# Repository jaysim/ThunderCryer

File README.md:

ThunderCryer
============

Alarm Clock 

new Variant started from scratch using ChibiosRT and uGFX

Modtivation is to get a more cleaner implementation and save time implenting a Graphics System. 

Plan is to use Chibios HAL as far as possible and use STM32USB_Host lib for MSC Host implementation

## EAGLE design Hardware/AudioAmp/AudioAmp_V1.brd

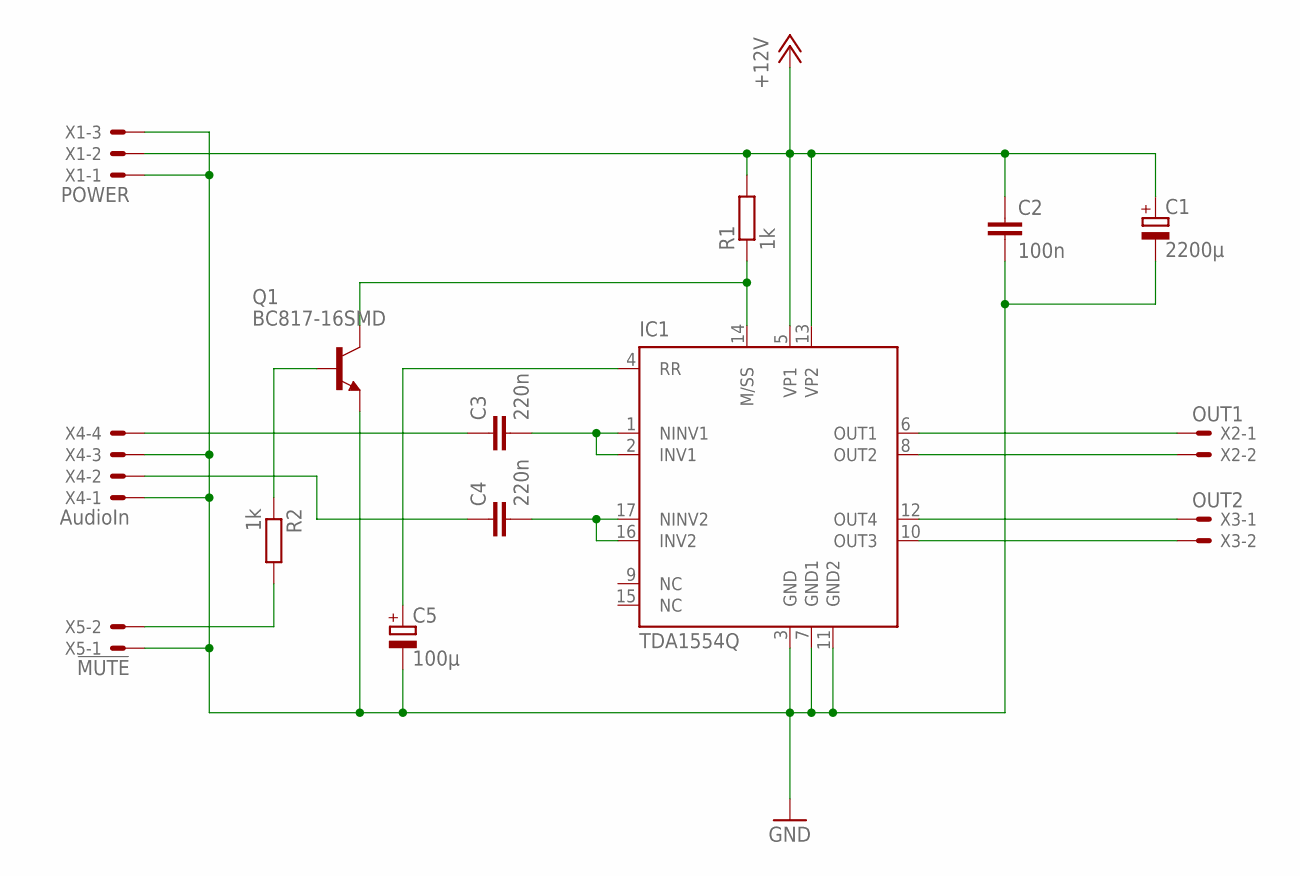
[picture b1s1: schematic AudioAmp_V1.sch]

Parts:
C1: 2200µ; E7,5-18
C2: 100n; C050-025X075
C3, C4: 220n; C050-025X075
C5: 100µ; E2,5-7
IC1: TDA1554Q; MULTIWAT-SIL17
Q1: BC817-16SMD; SOT23-BEC
R1, R2: 1k; 0204/7
X1: POWER; 22-23-2031
X2: OUT1; 22-23-2021
X3: OUT2; 22-23-2021
X4: AudioIn; 22-23-2041
X5: !MUTE; 22-23-2021

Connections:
+12V: C1.+, C2.1, IC1.5 (VP1), IC1.13 (VP2), R1.2, X1.2
GND: C1.-, C2.2, C5.-, IC1.3 (GND), IC1.7 (GND1), IC1.11 (GND2), Q1.E, X1.1, X1.3, X4.1, X4.3, X5.1
unnamed: C3.2, IC1.1 (NINV1), IC1.2 (INV1)
unnamed: C4.2, IC1.16 (INV2), IC1.17 (NINV2)
unnamed: R2.2, X5.2
unnamed: C4.1, X4.2
unnamed: C3.1, X4.4
unnamed: C5.+, IC1.4 (RR)
unnamed: Q1.B, R2.1
unnamed: IC1.10 (OUT3), X3.2
unnamed: IC1.12 (OUT4), X3.1
unnamed: IC1.8 (OUT2), X2.2
unnamed: IC1.6 (OUT1), X2.1
unnamed: IC1.14 (M/SS), Q1.C, R1.1

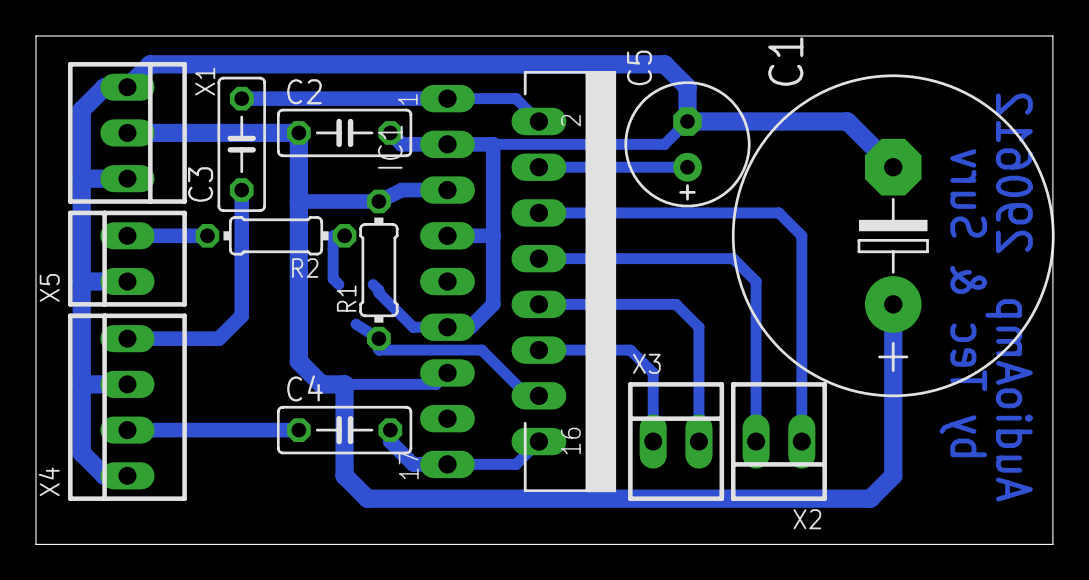
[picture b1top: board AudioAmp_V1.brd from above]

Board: 2 copper layers, 56.5 x 28.2 mm, 14 parts (1 on the bottom side), 14 nets.

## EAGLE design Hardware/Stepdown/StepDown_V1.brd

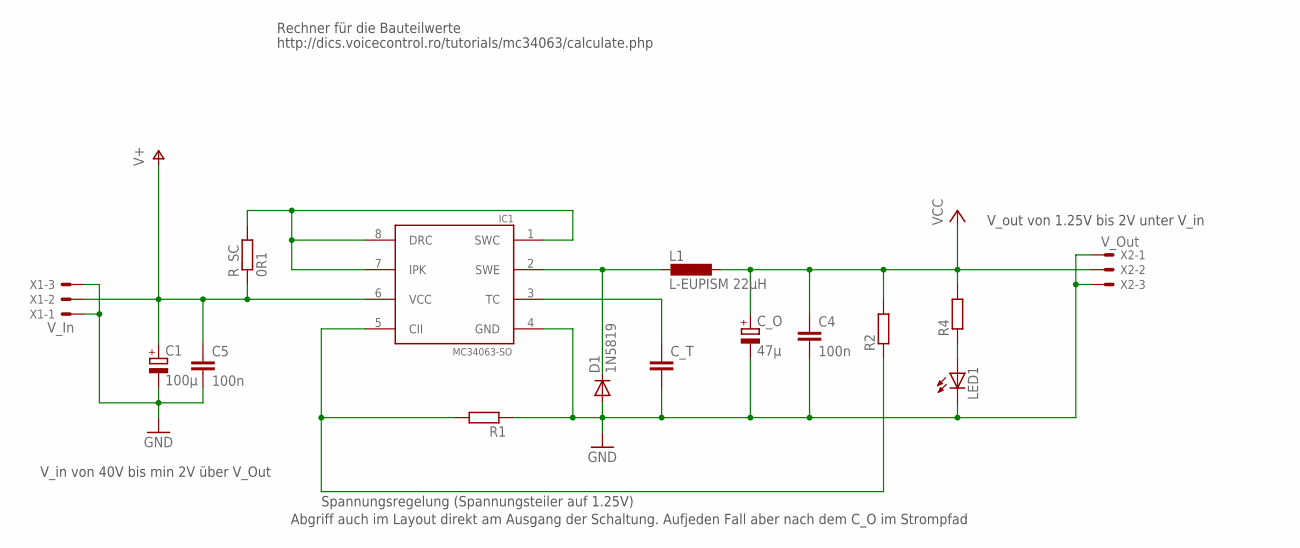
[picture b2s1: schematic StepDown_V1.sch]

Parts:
C1: 100µ; E2,5-7
C4, C5: 100n; C1206
C_O: 47µ; E2,5-7
C_T: C-EUC1206; C1206
D1: 1N5819; DO41-10
IC1: MC34063-SO; SO8
L1: L-EUPISM 22µH; PISM
LED1: LEDSML1206; SML1206
R1, R2, R4: R-EU_R1206; R1206
R_SC: 0R1; R1206
X1: V_In; 22-23-2031
X2: V_Out; 22-23-2031

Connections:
GND: C1.-, C4.2, C5.2, C_O.-, C_T.2, D1.A, IC1.4 (GND), LED1.C, R1.1, X1.1, X1.3, X2.1, X2.3
unnamed: IC1.1 (SWC), IC1.7 (IPK), IC1.8 (DRC), R_SC.2
unnamed: D1.C, IC1.2 (SWE), L1.2
unnamed: LED1.A, R4.1
unnamed: IC1.5 (CII), R1.2, R2.1
unnamed: C_T.1, IC1.3 (TC)
V+: C1.+, C5.1, IC1.6 (VCC), R_SC.1, X1.2
VCC: C4.1, C_O.+, L1.1, R2.2, R4.2, X2.2

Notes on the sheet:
http://dics.voicecontrol.ro/tutorials/mc34063/calculate.php
Rechner für die Bauteilwerte
V_in von 40V bis min 2V über V_Out
V_out von 1.25V bis 2V unter V_in
Spannungsregelung (Spannungsteiler auf 1.25V)
Abgriff auch im Layout direkt am Ausgang der Schaltung. Aufjeden Fall aber nach dem C_O im Strompfad

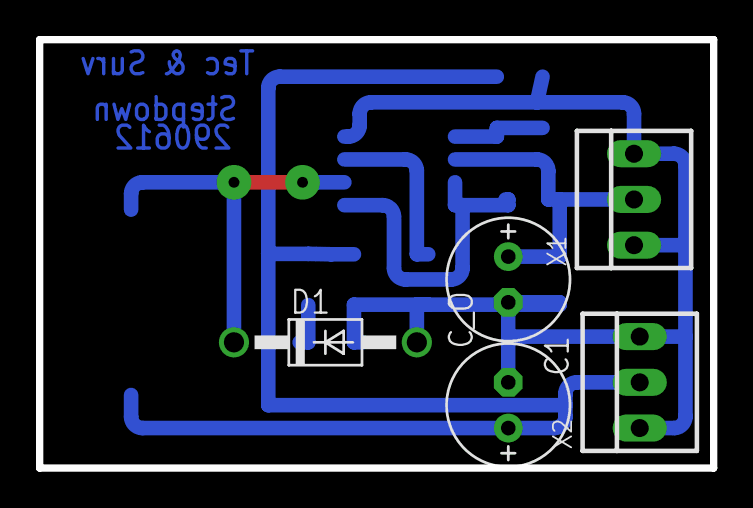
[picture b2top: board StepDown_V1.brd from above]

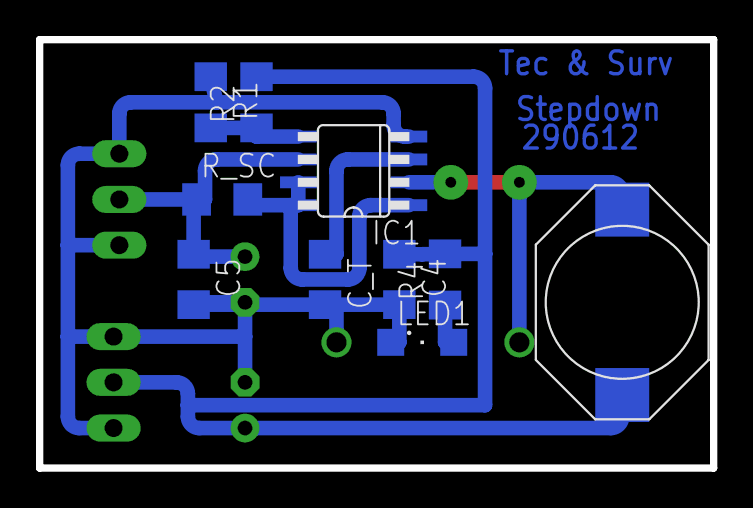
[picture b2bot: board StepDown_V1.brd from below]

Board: 2 copper layers, 37.4 x 23.8 mm, 15 parts (10 on the bottom side), 8 nets.

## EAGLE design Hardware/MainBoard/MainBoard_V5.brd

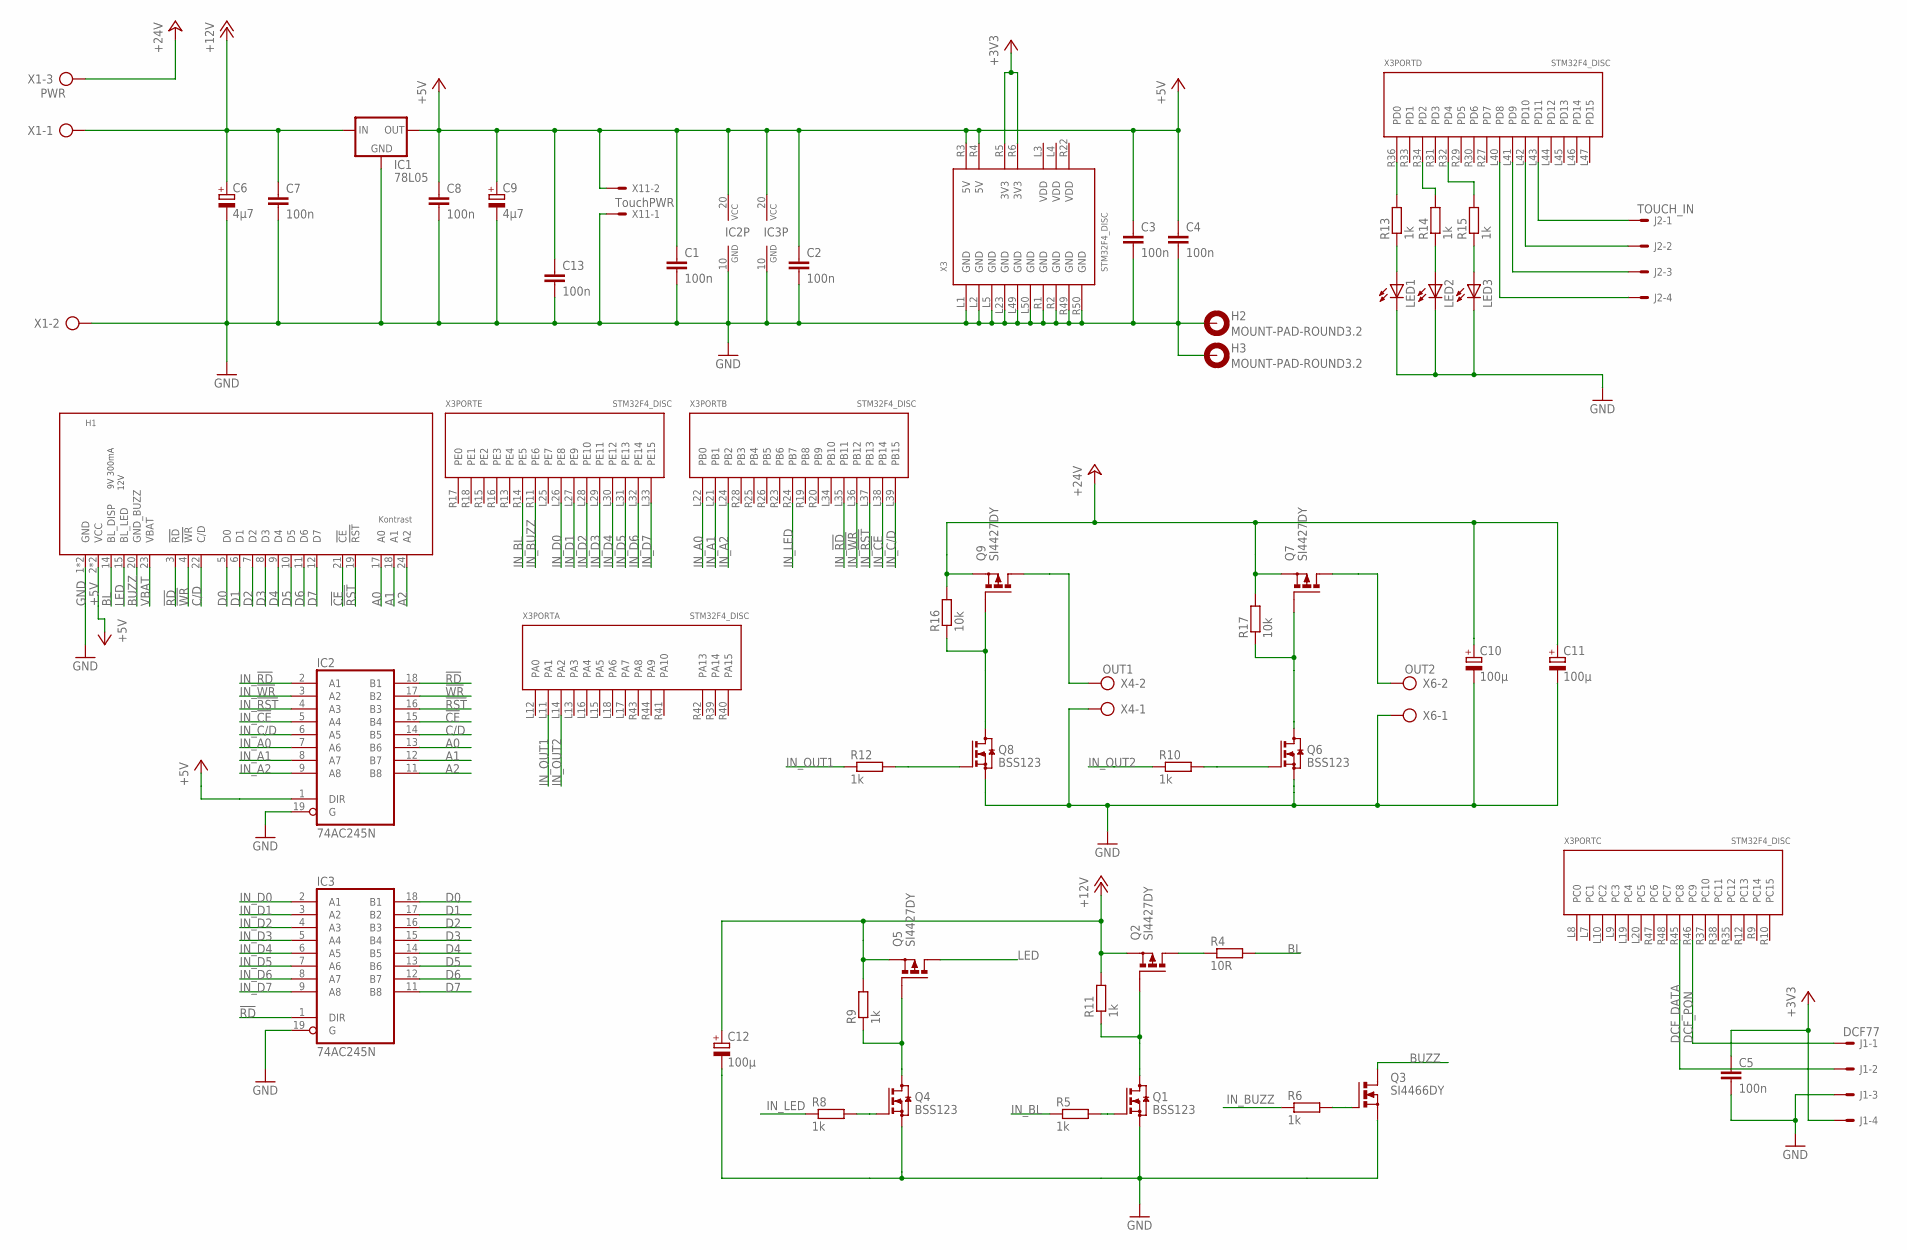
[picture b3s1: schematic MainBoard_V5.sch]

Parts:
C1, C2, C3, C4, C5, C7, C8, C13: 100n; C1206
C6, C9: 4µ7; E2-5
C10, C11, C12: 100µ; E2-5
H1: YL_24012-70-MICROMATCH; YL24012-70-MICROMATCH
H2, H3: MOUNT-PAD-ROUND3.2; 3,2-PAD
IC1: 78L05; 78XXS
IC2, IC3: 74AC245N; DIL20
J1: DCF77; 6410-04
J2: TOUCH_IN; 6410-04
LED1, LED2, LED3: LED3MM
Q1, Q4, Q6, Q8: BSS123; SOT23
Q2, Q5, Q7, Q9: SI4427DY; SO-08
Q3: SI4466DY; SO-08
R4: 10R; 0414/15
R5, R8, R9, R10, R11, R12, R13, R14, R15: 1k; 0207/10
R6: 1k; R0805
R16, R17: 10k; R1206
X1: PWR; AK500/3
X3: STM32F4_DISC
X4: OUT1; AK500/2
X6: OUT2; AK500/2
X11: TouchPWR; 22-23-2021

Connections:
!CE: H1.21 (!CE), IC2.15 (B4)
!RD: H1.3 (!RD), IC2.18 (B1), IC3.1 (DIR)
!RST: H1.19 (!RST), IC2.16 (B3)
!WR: H1.4 (!WR), IC2.17 (B2)
+3V3: C5.1, J1.4, X3.R5 (3V3), X3.R6 (3V3)
+5V: C1.1, C2.1, C3.1, C4.1, C8.1, C9.+, C13.1, H1.2 (VCC), H1.16 (VCC), IC1.OUT, IC2.1 (DIR), IC2.20 (VCC), IC3.20 (VCC), X3.R3 (5V), X3.R4 (5V), X11.2
+12V: C6.+, C7.1, C12.+, IC1.IN, Q2.1 (S), Q2.2 (S), Q2.3 (S), Q5.1 (S), Q5.2 (S), Q5.3 (S), R9.2, R11.2, X1.1
+24V: C10.+, C11.+, Q7.1 (S), Q7.2 (S), Q7.3 (S), Q9.1 (S), Q9.2 (S), Q9.3 (S), R16.2, R17.2, X1.3
A0: H1.17 (A0), IC2.13 (B6)
A1: H1.18 (A1), IC2.12 (B7)
A2: H1.24 (A2), IC2.11 (B8)
BL: H1.14 (BL_DISP), R4.2
BUZZ: H1.20 (GND_BUZZ), Q3.5 (D), Q3.6 (D), Q3.7 (D), Q3.8 (D)
C/D: H1.22 (C/D), IC2.14 (B5)
D0: H1.5 (D0), IC3.18 (B1)
D1: H1.6 (D1), IC3.17 (B2)
D2: H1.7 (D2), IC3.16 (B3)
D3: H1.8 (D3), IC3.15 (B4)
D4: H1.9 (D4), IC3.14 (B5)
D5: H1.10 (D5), IC3.13 (B6)
D6: H1.11 (D6), IC3.12 (B7)
D7: H1.12 (D7), IC3.11 (B8)
DCF_DATA: J1.2, X3.R45 (PC8)
DCF_PON: J1.1, X3.R46 (PC9)
GND: C1.2, C2.2, C3.2, C4.2, C5.2, C6.-, C7.2, C8.2, C9.-, C10.-, C11.-, C12.-, C13.2, H1.1 (GND), H1.13 (GND), H2.B3,2, H3.B3,2, IC1.GND, IC2.10 (GND), IC2.19 (G), IC3.10 (GND), IC3.19 (G), J1.3, LED1.K (C), LED2.K (C), LED3.K (C), Q1.2 (S), Q3.1 (S), Q3.2 (S), Q3.3 (S), Q4.2 (S), Q6.2 (S), Q8.2 (S), X1.2, X3.L1 (GND), X3.L2 (GND), X3.L5 (GND), X3.L23 (GND), X3.L49 (GND), X3.L50 (GND), X3.R1 (GND), X3.R2 (GND), X3.R49 (GND), X3.R50 (GND), X4.1, X6.1, X11.1
IN_!CE: IC2.5 (A4), X3.L38 (PB14)
IN_!RD: IC2.2 (A1), X3.L35 (PB11)
IN_!RST: IC2.4 (A3), X3.L37 (PB13)
IN_!WR: IC2.3 (A2), X3.L36 (PB12)
IN_A0: IC2.7 (A6), X3.L22 (PB0)
IN_A1: IC2.8 (A7), X3.L21 (PB1)
IN_A2: IC2.9 (A8), X3.L24 (PB2)
IN_BL: R5.1, X3.R14 (PE5)
IN_BUZZ: R6.1, X3.R11 (PE6)
IN_C/D: IC2.6 (A5), X3.L39 (PB15)
IN_D0: IC3.2 (A1), X3.L26 (PE8)
IN_D1: IC3.3 (A2), X3.L27 (PE9)
IN_D2: IC3.4 (A3), X3.L28 (PE10)
IN_D3: IC3.5 (A4), X3.L29 (PE11)
IN_D4: IC3.6 (A5), X3.L30 (PE12)
IN_D5: IC3.7 (A6), X3.L31 (PE13)
IN_D6: IC3.8 (A7), X3.L32 (PE14)
IN_D7: IC3.9 (A8), X3.L33 (PE15)
IN_LED: R8.1, X3.R24 (PB7)
IN_OUT1: R12.1, X3.L11 (PA1)
IN_OUT2: R10.1, X3.L14 (PA2)
LED: H1.15 (BL_LED), Q5.5 (D), Q5.6 (D), Q5.7 (D), Q5.8 (D)
unnamed: R15.2, X3.R32 (PD4)
unnamed: R14.2, X3.R34 (PD2)
unnamed: J2.1, X3.L43 (PD11)
unnamed: Q1.3 (D), Q2.4 (G), R11.1
unnamed: Q2.5 (D), Q2.6 (D), Q2.7 (D), Q2.8 (D), R4.1
unnamed: Q1.1 (G), R5.2
unnamed: Q4.3 (D), Q5.4 (G), R9.1
unnamed: Q3.4 (G), R6.2
unnamed: J2.2, X3.L42 (PD10)
unnamed: J2.3, X3.L41 (PD9)
unnamed: Q4.1 (G), R8.2
unnamed: Q6.3 (D), Q7.4 (G), R17.1
unnamed: Q6.1 (G), R10.2
unnamed: J2.4, X3.L40 (PD8)
unnamed: Q8.3 (D), Q9.4 (G), R16.1
unnamed: Q8.1 (G), R12.2
unnamed: LED1.A, R13.1
unnamed: LED2.A, R14.1
unnamed: LED3.A, R15.1
unnamed: R13.2, X3.R36 (PD0)
OUT1: Q9.5 (D), Q9.6 (D), Q9.7 (D), Q9.8 (D), X4.2
OUT2: Q7.5 (D), Q7.6 (D), Q7.7 (D), Q7.8 (D), X6.2
VBAT: H1.23 (VBAT)
VDD: X3.L3 (VDD), X3.L4 (VDD), X3.R22 (VDD)

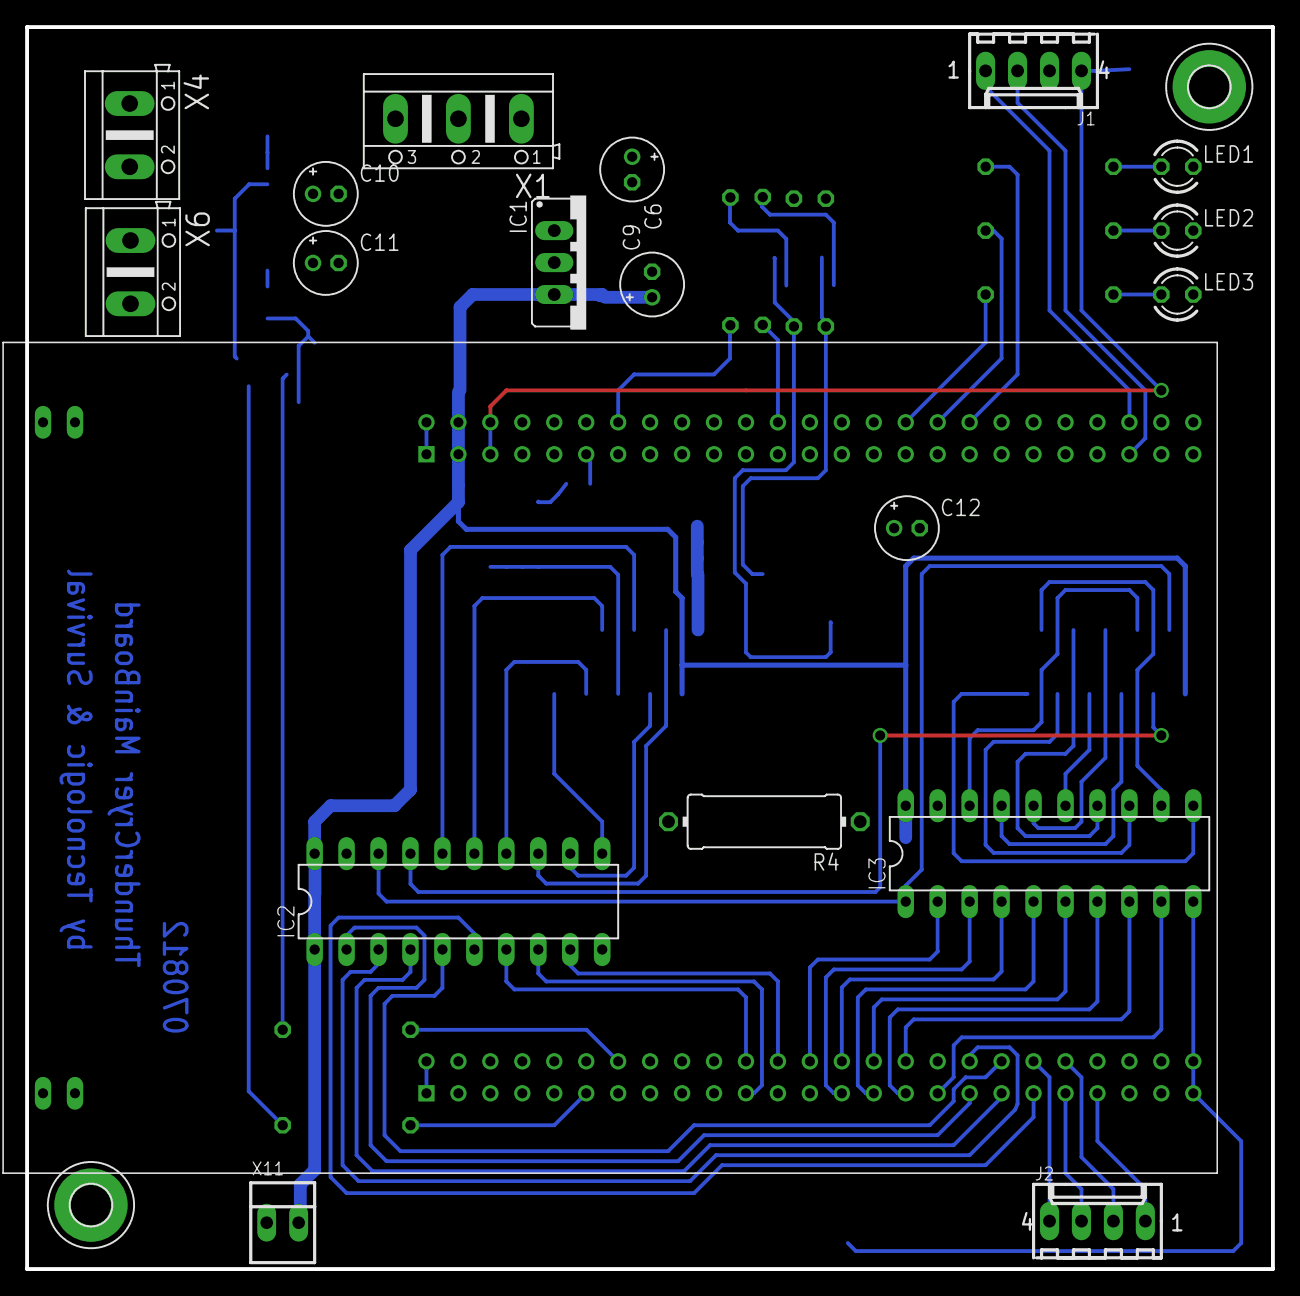
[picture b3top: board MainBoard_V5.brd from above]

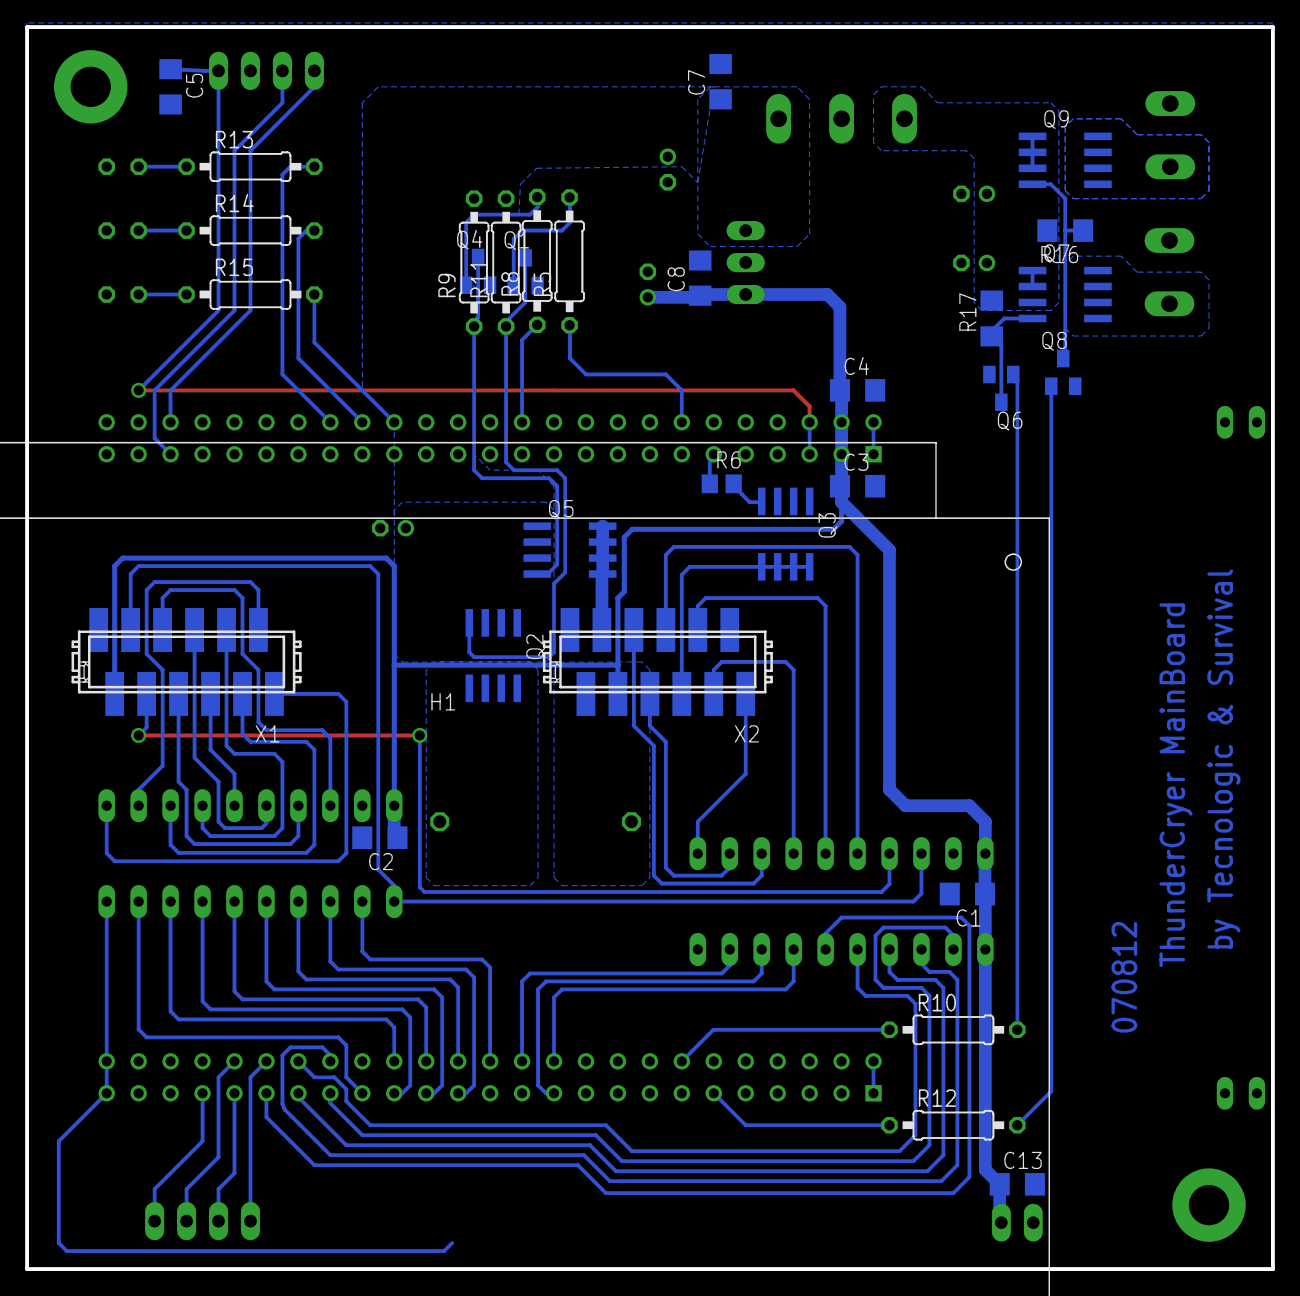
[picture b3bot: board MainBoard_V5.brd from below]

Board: 2 copper layers, 99.0 x 98.7 mm, 51 parts (30 on the bottom side), 70 nets.

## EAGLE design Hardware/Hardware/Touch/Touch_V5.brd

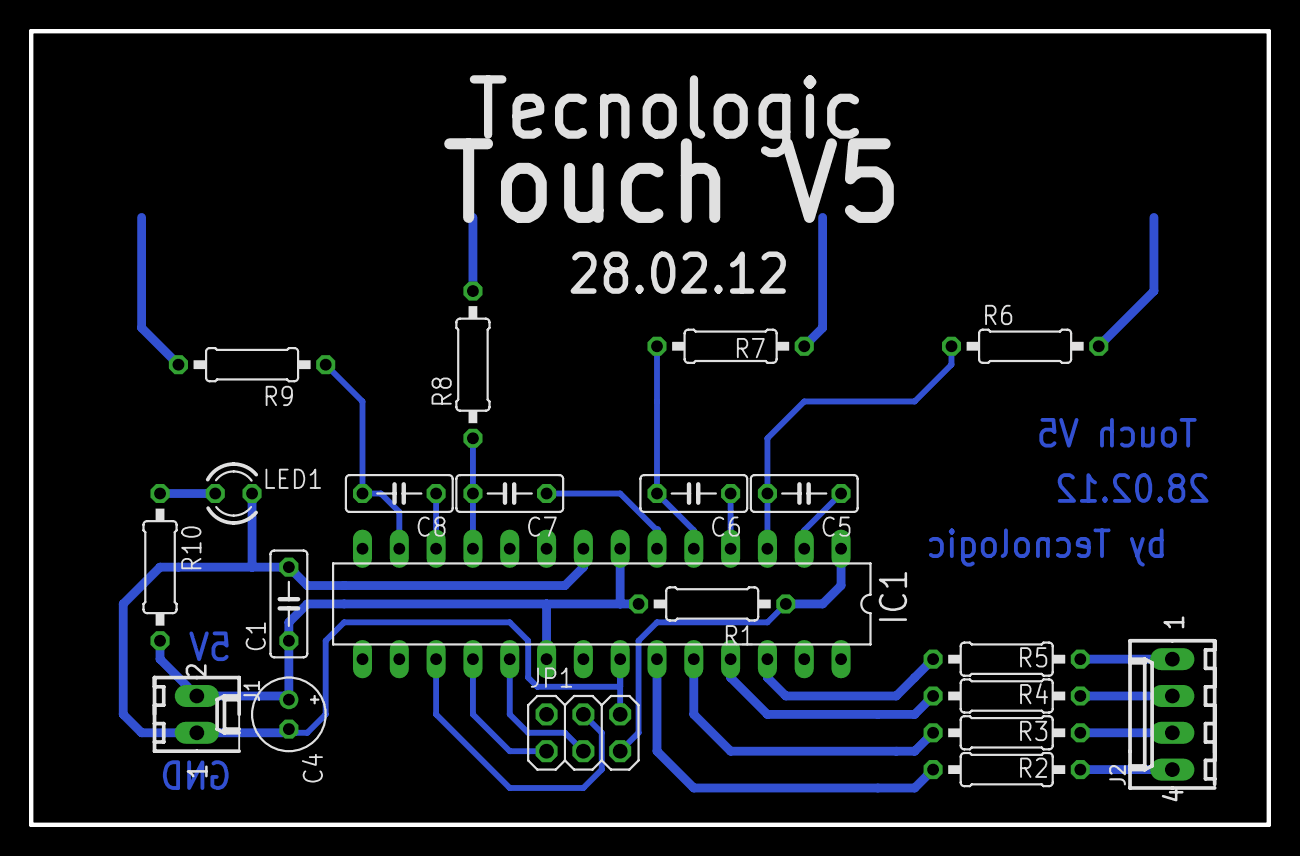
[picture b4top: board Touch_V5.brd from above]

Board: 2 copper layers, 85.4 x 54.8 mm, 21 parts (0 on the bottom side), 23 nets.

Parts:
C1: 100n; C050-025X075
C4: 10µ; E2-5
C5, C6, C7, C8: 47n; C050-025X075
IC1: MEGA48-P; DIL28-3
J1: 22-27-2021-02; 6410-02
J2: 22-27-2041-04; 6410-04
JP1: ISP; 2X03
LED1: PWR; LED3MM
R1: 10K; 0207/10
R2, R3, R4, R5, R6, R7, R8, R9, R10: 1k; 0207/10

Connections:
GND: C1.2, C4.-, IC1.8, IC1.22, J1.1, JP1.6, LED1.K
MISO: IC1.18, JP1.1
MOSI: IC1.17, JP1.4
unnamed: J2.4, R2.2
unnamed: J2.3, R3.2
unnamed: J2.2, R4.2
unnamed: J2.1, R5.2
unnamed: LED1.A, R10.1
OUT1: IC1.23, R2.1
OUT2: IC1.24, R3.1
OUT3: IC1.25, R4.1
OUT4: IC1.26, R5.1
RESET: IC1.1, JP1.5, R1.1
SCK: IC1.19, JP1.3
SNS0: C5.1, IC1.2
SNS1: C6.1, IC1.4
SNS2: C7.1, IC1.6
SNS3: C8.1, IC1.12
SNSK0: C5.2, IC1.3, R6.1
SNSK1: C6.2, IC1.5, R7.1
SNSK2: C7.2, IC1.11, R8.1
SNSK3: C8.2, IC1.13, R9.1
VCC: C1.1, C4.+, IC1.7, IC1.20, J1.2, R1.2, R10.2

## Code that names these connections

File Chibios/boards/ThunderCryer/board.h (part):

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 * GPIOA setup:
 *
 * PA0  - BUTTON                    (input floating).
 * PA1  - OUT1                      (output pushpull maximum).
 * PA2  - OUT2                      (output pushpull maximum).
 * PA3  - PIN3                      (input pullup).
 * PA4  - LRCK                      (alternate 6).
 * PA5  - SPC                       (alternate 5).
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/*
 * GPIOB setup:
 *
 * PB0  - CONTRAST_A0               (output pushpull maximum).
 * PB1  - CONTRAST_A1               (output pushpull maximum).
 * PB2  - CONTRAST_A2               (output pushpull maximum).
 * PB3  - SWO                       (alternate 0).
 * PB4  - PIN4                      (input pullup).
 * PB5  - PIN5                      (input pullup).
 * PB6  - SCL                       (alternate 4).
 * PB7  - LED                       (output pushpull maximum).
 * PB8  - PIN8                      (input pullup).
 * PB9  - SDA                       (alternate 4).
 * PB10 - CLK_IN                    (input pullup).
 * PB11 - RD                        (output pushpull maximum).
 * PB12 - WR                        (output pushpull maximum).
 * PB13 - RST                       (output pushpull maximum).
 * PB14 - CE                        (output pushpull maximum).
 * PB15 - CD                        (output pushpull maximum).
 */
#define VAL_GPIOB_MODER             (PIN_MODE_OUTPUT(GPIOB_CONTRAST_A0) |   \
                                     PIN_MODE_OUTPUT(GPIOB_CONTRAST_A1) |   \
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 * PC5  - PIN5                      (input pullup).
 * PC6  - PIN6                      (input pullup).
 * PC7  - MCLK                      (alternate 6).
 * PC8  - DCF_DATA                  (input pullup).
 * PC9  - DCF_PON                   (output pushpull maximum).
 * PC10 - SCLK                      (alternate 6).
 * PC11 - PIN11                     (input pullup).
 * PC12 - SDIN                      (alternate 6).
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/*
 * GPIOD setup:
 *
 * PD0  - TC_LED1                   (output pushpull maximum).
 * PD1  - TC_LED2                   (output pushpull maximum).
 * PD2  - TC_ED3                    (output pushpull maximum).
 * PD3  - PIN3                      (input pullup).
 * PD4  - RESET                     (output pushpull maximum).
 * PD5  - OVER_CURRENT              (input floating).
 * PD6  - PIN6                      (input pullup).
 * PD7  - PIN7                      (input pullup).
 * PD8  - TOUCH_LEFT                (input pullup).
 * PD9  - TOUCH_UP                  (input pullup).
 * PD10 - TOUCH_DOWN                (input pullup).
 * PD11 - TOUCH_RIGHT               (input pullup).
 * PD12 - LED4                      (output pushpull maximum).
 * PD13 - LED3                      (output pushpull maximum).
 * PD14 - LED5                      (output pushpull maximum).
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 * PE2  - PIN2                      (input floating).
 * PE3  - CS_SPI                    (output pushpull maximum).
 * PE4  - PIN4                      (input floating).
 * PE5  - LCD_BACKLIGHT             (alternate 3).
 * PE6  - BUZZER                    (output pushpull maximum).
 * PE7  - PIN7                      (input floating).
 * PE8  - D0                        (output pushpull maximum).
 * PE9  - D1                        (output pushpull maximum).
 * PE10 - D2                        (output pushpull maximum).
 * PE11 - D3                        (output pushpull maximum).
 * PE12 - D4                        (output pushpull maximum).
 * PE13 - D5                        (output pushpull maximum).
 * PE14 - D6                        (output pushpull maximum).
 * PE15 - D7                        (output pushpull maximum).
 */
#define VAL_GPIOE_MODER             (PIN_MODE_INPUT(GPIOE_INT1) |           \
                                     PIN_MODE_INPUT(GPIOE_INT2) |           \
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
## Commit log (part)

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2012-02-14 Initial Commit for testing purposes.
    Cpp, FreeRTOS, STM32F4 Discovery template
2012-02-14 Led Task finshed
    On Board Leds flash in clockwise direction.
2012-02-14 changed top commend in main.cpp
2012-02-14 asm nop test
2012-02-14 added hardware
    eagle schematic and board not finished but started
2012-02-14 Added T6963C Driver written in C
    basis for port to C++ graphics lib for T6963C Display
2012-02-14 changed CG in GLCD Lib
2012-02-15 initial LedHeartBeat + App Hooks for on board Micro
2012-02-17 added Graphics LCD Driver Classes
    unfinished
2012-02-17 Doxygen comments
2012-02-18 Finished GPIO Driver
2012-02-18 finished build with Graphics LCD Classes
2012-02-18 Display Test with compile errors
2012-02-18 made all pure virtual methods in GLCD Driver really pure virtual
    = 0; at the end of function declaration
2012-02-19 changed linker skript to attolic
2012-02-19 first run with cpp
    attolic was the cure
2012-02-23 added FatFS
2012-02-23 added SDIO function from new ST std perph driver examples
2012-02-23 changed to fatfs 0.08b
2012-02-23 first succsessful fatfs compile
2012-02-23 added all files to git index
2012-02-23 added remove unused section linker flag
2012-02-23 Fatfs test finished
    lets give it a try
2012-02-23 switched pulldown on GLCD Data Pins on
2012-02-23 reduced delay times in glcd driver
    data read fails sometimes
    Pulldonws an better delay hopefully solve this problem
2012-02-23 changed order of pin writes in glcd read data
    data read process needs hardware debuging, unlikely an sw problem
2012-02-23 added HelixMp3 decoder
    compiles succsessful
2012-02-24 Set pixel now sets resets a pixel directly
    old implementation was to complicated
2012-02-24 Added Sansserif Font
2012-02-24 implemented small demonstration
2012-02-24 added window shadow
2012-02-25 Display Driver ready to run
2012-02-28 SDIO Test with pullups giving SD_OK
    Fs -> FR_NOT_READY
2012-02-28 FatFs test, disk_read SD_ADR_MISSALLIGNMED
2012-02-29 FATFS ready
    Check discription for SD READ BLOCk
2012-03-04 Complile thinned
    removed unused stlib files from build
2012-03-05 Started with Mp3 Test Changed FatFS Read and write to multi block operations
    Fatfs multiblock operation untested
2012-03-06 Updated Filehandler tast to play mp3 file
2012-03-10 changed Massstorage interface to USB_OTG Host
    Compile and Test Ok
    starting integrating
2012-03-10 Usb Task Wrapper Class introduced
2012-03-10 USB Tast now gives Semaphore when device mounted
    File handler needs to manage this
2012-03-11 changed FatFS to Longfilename
2012-03-11 Fatfs was not reentrant
    changes option
2012-03-11 just finished play mp3 function
2012-03-12 MP3 Audio with Helix no Output
    Fail on asambly instructions
2012-03-14 Changed Assembly.h to Cortex M3 version from Stellarisforum
2012-03-15 Changed Buffersize to number of bytes für Mal_Play
2012-03-17 Mp3 Playing good
    noise on starting mp3 playing, Codec
2012-05-11 - removed USB Mounted Sem - Filehandler prepared for MP3Player
2012-05-14 started MP3Playerstatemachine
2012-05-14 minor changes to MP3Player
    - Usb Stack sem was not used, corrected
2012-05-16 Mp3Player beta stage - initI2s with fixed rates for 44100 and 48000 needs a check up
2012-05-16 initial commit of CRTCHandler Class for RTC and alarm handling
2012-05-16 added basic task functions, RTC init will be in Hardwareinit function
2012-05-16 commented warning sources, (unused function/variable)
2012-05-16 added basic function to RTC Task
2012-07-27 Added CTime, a wrapper for time.h
2012-07-28 Added Cpp Lib hacks from Andy Brown
2012-07-28 nothing serious
2012-08-02 added Path Clock to Paths an Symbols
2012-08-30 Start of GUI Development
2012-08-30 Added first GUI structure with base classes
2012-08-31 Started GUI base class and api implementation for GUI objects
2012-09-03 GUI Base Classes implementation finished
2012-09-04 finished implementation of actor Button
2012-09-04 added display pointer to page and actor base class
2012-09-04 unfinished base implementation of Numberswitch Actor
2012-09-04 added focus to button
2013-01-31 initial commit of basic GUI elements
2013-02-05 kicked FreeRTOS
2013-02-05 added base config files for ChibiOSRT
2013-02-05 renamed Heartbeat thread recources
2013-02-05 added ChibiOS style makefile
2013-02-05 chibios compile ready
2013-02-07 ported Heartbeat task to chibios cpp wrapper
2013-02-07 managedtask was changed to template, no good implementation
2013-02-19 added prj folder, with CrossWorks project files
2013-02-19 removed unused files
2013-02-20 added implematation of __assert function
2013-02-20 added asset definition
2013-02-20 Crossworks test setup
2013-02-24 added ChibiOS/RT as Submodule
2013-02-28 added gitignore script
2013-02-28 set process stack from 0 to 256 bytes and heap to 32k
2013-02-28 changed disp to lowest prio
2013-02-28 Readded missing Hardware Files
2013-03-05 updated gitignore
2013-03-05 added delay in Task function to yield power to other processes
2013-03-05 updated pinning for lcd
    according to Mainboard rev V5
2013-03-05 only saved
2013-03-05 saves
2013-03-06 Dont turn on External Display LEDs
2013-03-21 corrected task stack monitoring
    display remaining stack in bytes
2013-03-21 added runtime stats to threads window
2013-03-21 updated with runtime available, changed taskYield
    - added ulRunTimeCounter as global to get runtime stats in crossworks
    - changed taskYield to delay each delay cycle.
2013-03-21 raised tickrate to 1000Hz
2013-06-20 reactivated project
2013-06-20 enable Crossworks to view FreeRtos Threads
2013-06-20 corrected FreeRTOS Thread script
2013-06-20 updated rom c-convention to c++
2013-06-20 changed task setup
2013-06-20 changed stack and heap size
2013-06-20 added flash_placement file
2013-06-24 finaly fixed the missing closing brance
    of an extern c definition
2013-07-14 added ccm ram usage
2013-07-14 excluded usb device files from build
2013-07-17 recent build with ccram
2013-07-17 new project setup
2013-07-17 ignore doku
2013-07-18 set heap and stack size
2013-07-18 taken startup from mifi
2013-07-18 Revert "taken startup from mifi"
    This reverts commit 9a42dddac068f766962ced8f0f2807c85d7556a5.
2013-07-18 taken lds from mifi and modified heap and stack placement to CCram
2013-07-18 Moved HelixMP3 to AudioMP3
2013-07-18 renamed Audio_MP3 to Audio
2013-07-18 moved FATFS and USB_MSC to USB-HOST-Lib
2013-07-18 moved Filehandler and fattime to usb_msc
2013-07-18 moved helix to top level
2013-07-18 adding source files, unfinished jet
2013-07-21 added src files
2013-07-22 rename to small .s
2013-07-22 cpp compile un correct
2013-07-22 excluded assert
2013-07-22 finaly make file builds the sw
2013-07-22 ignore build files
2013-07-23 cleaned Project
2013-07-23 added Chibios Files
2013-07-23 added files from stm32f4 disc example
2013-07-23 added T6963C Files as disply driver to gfx
2013-07-23 included gfxconf.h example to project
2013-07-23 integrated uGFX in makefile
2013-07-23 fixed makefile for main.cpp
2013-07-23 added build to ignore
2013-07-24 finished Board config
2013-07-24 finished board config with generation of Board.h board.c board.mk
2013-07-25 configured gfx and ch kernel
2013-07-25 cleaned T6963C driver Prepraration for lld
2013-07-25 renamed gfx board file
2013-07-25 initial setup for compile
2013-07-25 setup gfx
2013-07-27 rem other drivers
2013-07-27 started Board setup for BL PWM and delays for T6963C
2013-07-27 pwm for buzzer and backlight will be started with board init each channel will be activated seperatly by the according module
2013-07-27 added dilsplay driver define values
2013-07-27 finished port of t6963C display driver needs testing
2013-07-27 finished ginput driver
2013-07-27 fixed guar for pwmd9
2013-07-27 set ch_dynamic to true for uGFX
2013-07-27 changed setup to suppport gwin
2013-07-27 removed multiple drivers to prevent eclipse from using false headers
2013-07-27 compile fixes to the driver
2013-07-27 fixed the gfx config for compiling gwin
2013-07-27 removed test from main
2013-07-27 moved pwm config from board.c to gdisp cause buzzer is self swing type an does not need pwm
2013-07-27 added debug configs
2013-07-27 fixxed implicit declaration
2013-07-27 added tailing 0 to pwm config, compiler seems to want it
2013-07-27 raised initial BL to 100%
2013-07-27 changed contrast to 4 like old implementation
2013-07-28 fixed init pin levels for display
2013-07-28 finaly fixed the issue with the control lines the Bit definitions were bit positions
2013-07-28 console runs expanding lld driver to support faster fills
2013-08-12 changed to display hello msg and wait then
2013-08-12 added fatfs config
2013-08-12 added clock handling from trunk
2013-08-12 rem non usefull parts
2013-08-12 started rtc handler class
2013-08-12 added class discription
2013-09-02 added Highlevel Nottfier
2013-09-02 renamed an fixed files
2013-09-02 fixed compiler errors
2013-09-02 activated registry
2013-09-11 changed dcf tick to single task changed according functions to static
2013-09-12 made error free compile able
2013-09-12 added dcf77 task start
2013-09-12 added /Clock to includes
2013-09-16 implemented dcf newtime notyfication
2013-09-17 compile corrections regarding notifier
2013-09-17 added notification for one sec time of the day broadcast
2013-09-17 added rtc lib to compile
2013-09-24 alarm state machine implemented
2013-09-24 removed alarm handler from compile
2013-09-24 extended alarms to be skiped first compile
2013-09-24 compile issue changes
2013-09-24 added Timezone correction
2013-09-26 removed undefined UTC timezone = 0
2013-09-26 added lib hacks to prevent use of cpp lib functions adding code an unsupported functions
2013-09-26 added print of rtc notifications
2013-09-26 added libhacks and syscalls from chibios to compile
2013-09-26 added size print
2013-09-26 finaly size print is good:)
2013-09-29 made listeners stack vars of the thread function. to prevent false mem pool init for Notifier
2013-09-29 set malloc heap to true
2013-09-29 moved console and according handling to seperate thread to to unsufficient main thread stack
2013-09-29 disabled tillarea and clear functions. cause not correct implementated needs to be fixed
2013-09-30 moved ugfx and chibios to submodules
2013-09-30 removed un forked repos
2013-09-30 readded chibios as fork
2013-09-30 readded uGFX as fork from Bitbucket
2013-09-30 fixed font
2013-10-01 removed sequencer and used led for debug of dcf
2013-10-01 minor ugfx driver changes
2013-10-08 fixed display timeouts
2013-10-11 implemented rtc interrupt and alarm
2013-10-11 compile fixes to alarm commit
2013-10-11 activated exti driver
2013-10-11 fixed case error in CLightHandler.cpp as source
2013-10-11 added wakeup callback
2013-10-14 first port of usb cdc application as terminal
2013-10-14 updated display driver
2013-10-15 added cc3000 driver
2013-10-15 updated com driver with chprintf wrapper
2013-10-15 added main.h for global resource distribution
2013-10-15 added start of usb terminal
2013-10-15 nothing realy changed
2013-10-15 activated debug prints to usb console
2013-10-15 made rtcthread global
2013-10-15 added cast to prevent warning
2013-10-17 added wifi handler
2013-10-17 rem cross studio include
2013-10-17 added wifi handler files to compile
2013-10-17 added wifi task
2013-10-25 added Wifi to main
2013-10-26 added exti call back an driver settings for wifi
2013-10-26 getlocaltime redirect
2013-10-26 added cc3000 namespace
2013-10-26 added irq callback function to api
2013-10-26 added irq function to api
2013-10-26 updated rules mk to print size
2013-10-27 renamed Usb_terminal
2013-10-27 renamed Usb terminal, moved exti callback to main
2013-10-27 fixed namespacing made SDU2 global avail able for c code
2013-10-27 corrected namespacing utilised printf in stead of SDU2.print
2013-10-27 fixed namespacing
2013-10-27 fixed prints to use printf
2013-10-27 added sleep times
2013-10-27 removed bus accuire cause of call in interrupt
2013-10-27 raised wifi prio

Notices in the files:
Chibios/boards/ThunderCryer/board.h:
ChibiOS/RT - Copyright (C) 2006,2007,2008,2009,2010,
2011,2012 Giovanni Di Sirio.
